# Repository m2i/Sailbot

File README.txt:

Requirements:

Pi: Node.js v4.x.x
Base: Node.js 0.12.x

Instructions:

1. Connect both radios, make sure that both show a solid green light
2. Connect xbox wireless receiver
3. Connect xbox controller (make sure its paired with the receiver)
4. On the pi, navigate to ~/Documents/javascript
5. On the pi, run `sudo node index.js`
6. On the base station, navigate to wherever you pulled down the code
7. On the base station, run `node index.js`
8. Adjust the potentiometers so that neither servos are moving
9. You are now ready to use the xbox controller to control the servos.

Controls:

Right joystick - Main servo
Left joystick - Aft servo
Triggers - Rudder servo

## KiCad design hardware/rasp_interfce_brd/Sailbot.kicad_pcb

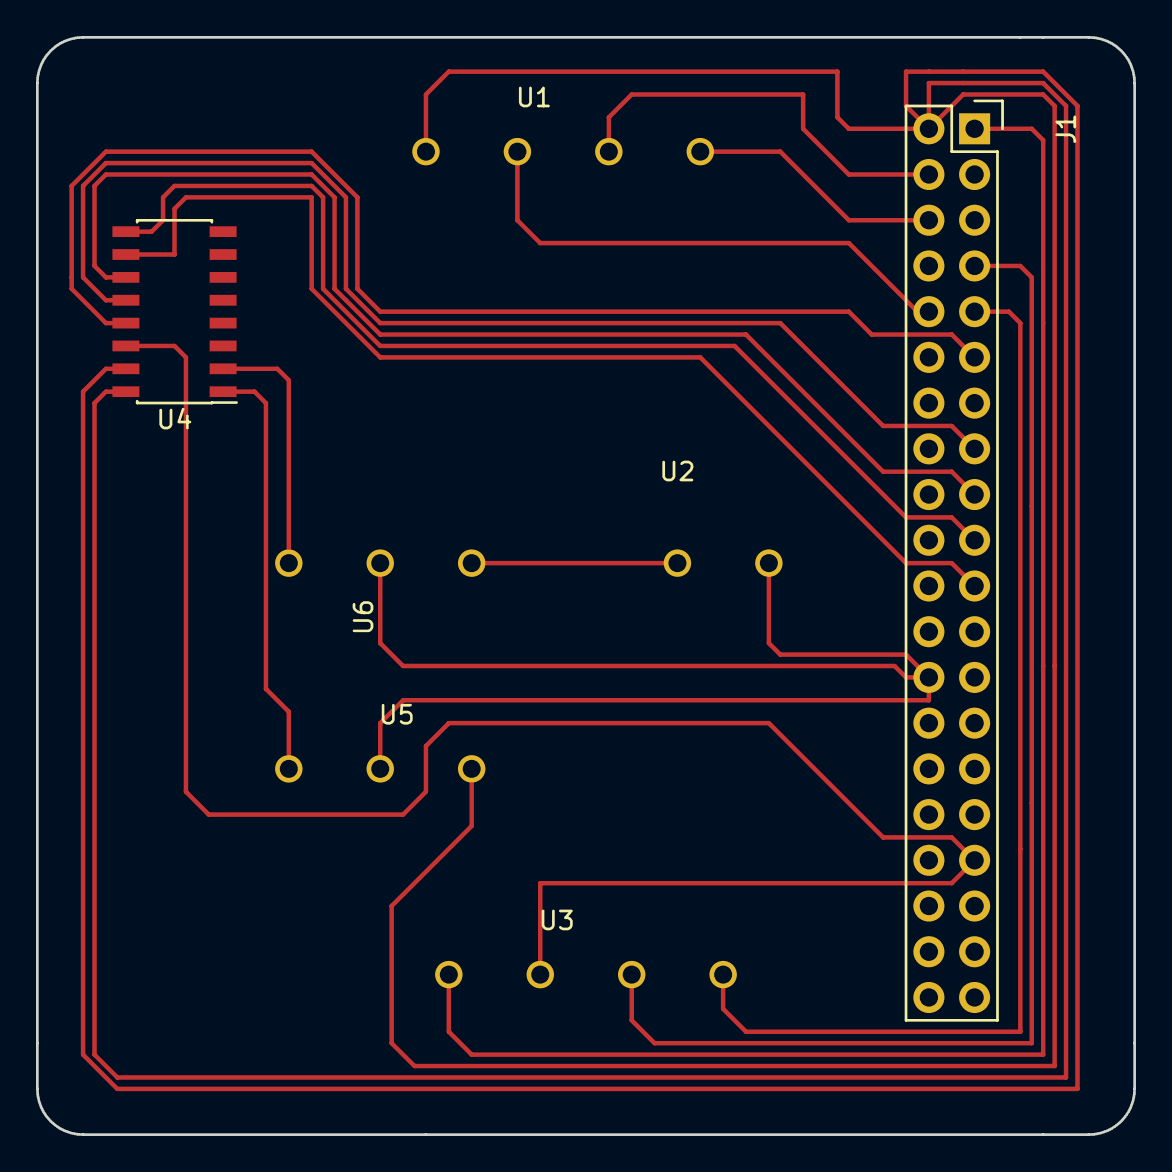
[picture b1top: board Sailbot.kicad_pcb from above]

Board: 2 copper layers, 61.0 x 61.0 mm, 7 parts (0 on the bottom side), 6 nets.

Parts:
J1: RPi_GPIO; Socket_Strip_Straight_2x20
U1: PWMController2; WindVane
U2: 7.2V
U3: Component; WindVane
U4: MCP3008; SOIC-16_3.9x9.9mm_Pitch1.27mm
U5: Windvane; WindVane
U6: Anemometer; WindVane

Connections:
GND: U1.2, U2.2, U3.2, U4.9, U4.14, U5.2, U6.2
unnamed: J1.1, U4.15, U4.16
unnamed: J1.18, U4.13
unnamed: J1.23, U4.12
unnamed: J1.24, U4.11
unnamed: J1.25, U4.10

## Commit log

2015-12-10 Initial commit (javascript)
2015-12-10 Initial commit (c)
2016-02-25 Milestone 1
2016-04-16 remove old arduino related code, add javascript
2016-04-21 channel switching
2016-04-28 xbox controller
2016-04-28 this might make the rudder work
2016-04-28 done - also added readme
2017-02-23 Added PCM Interface board for Raspberry Pi
